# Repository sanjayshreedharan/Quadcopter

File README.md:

# Quadcopter
An Indigenous Low cost Autopilot System for a Quadcopter using Arduino UNO/ FPGA.
 
This project endeavours to design a low cost indigenous auto-pilot system for a quadcopter using the Arduino UNO. This tutorial majorly deals only with the design and deployment of the autopilot system and we assume that you already have the frame, motors, ESC’s and the Lipo Batteries in place. This project also includes the PCB schematic on which our firmware is run.  

# Video

# Deployment Instructions
The frame can either be designed or it can be bought. For speedy development, if you don't have much time in your hands I would suggest to go with buying one. 

We obviously designed our own frame and since frame design and construction as such is a huge task, I would follow up with a tutorial for those of you who wish to design your own frames.

After the frame is ready, the next would be to get the motors, ESC’s, propellers and the power supply in place.The rating of the motors, ESC’s and power supply depends on the size of the frame and the pay-load capacity of the quadcopter. 

For autopilot, a 9DOF IMU (Inertial measurements unit), which consists of an accelerometer, gyroscope and a magnetometer is required. For wireless communication, Bluetooth or RC would do the job. We used the Bluetooth as we would be able to keep a watch on the state of the quadcopter through the serial monitor and also send commands. If flying low-heights and debugging is your requirement, go with bluetooth. For those of you who wish to fly great heights, use a RC module. 

The MPU6050 (6 DOF IMU with accelerometer and gyroscope) and HMC5883L(Magnetometer) was combined to give the quadcopter 9 degrees of freedom. The HC-06 module was used as bluetooth.

A custom Arduino UNO shield was designed for the purpose of a quadcopter. The schematic and the board design is available. So, if you know know how to make a PCB, you can make the shield with the MPU6050, HMC5883L and HC-06 on it and it would fit perfectly on top of the UNO.  

If making PCB is not your piece of cake, I would suggest you to connect the sensors with jumper wires. Make sure the connections, that you have made are reliable, if they are not this might pose a serious problem when the quadcopter is on the go.

After this is done, download the code and fuse it into your Arduino UNO.

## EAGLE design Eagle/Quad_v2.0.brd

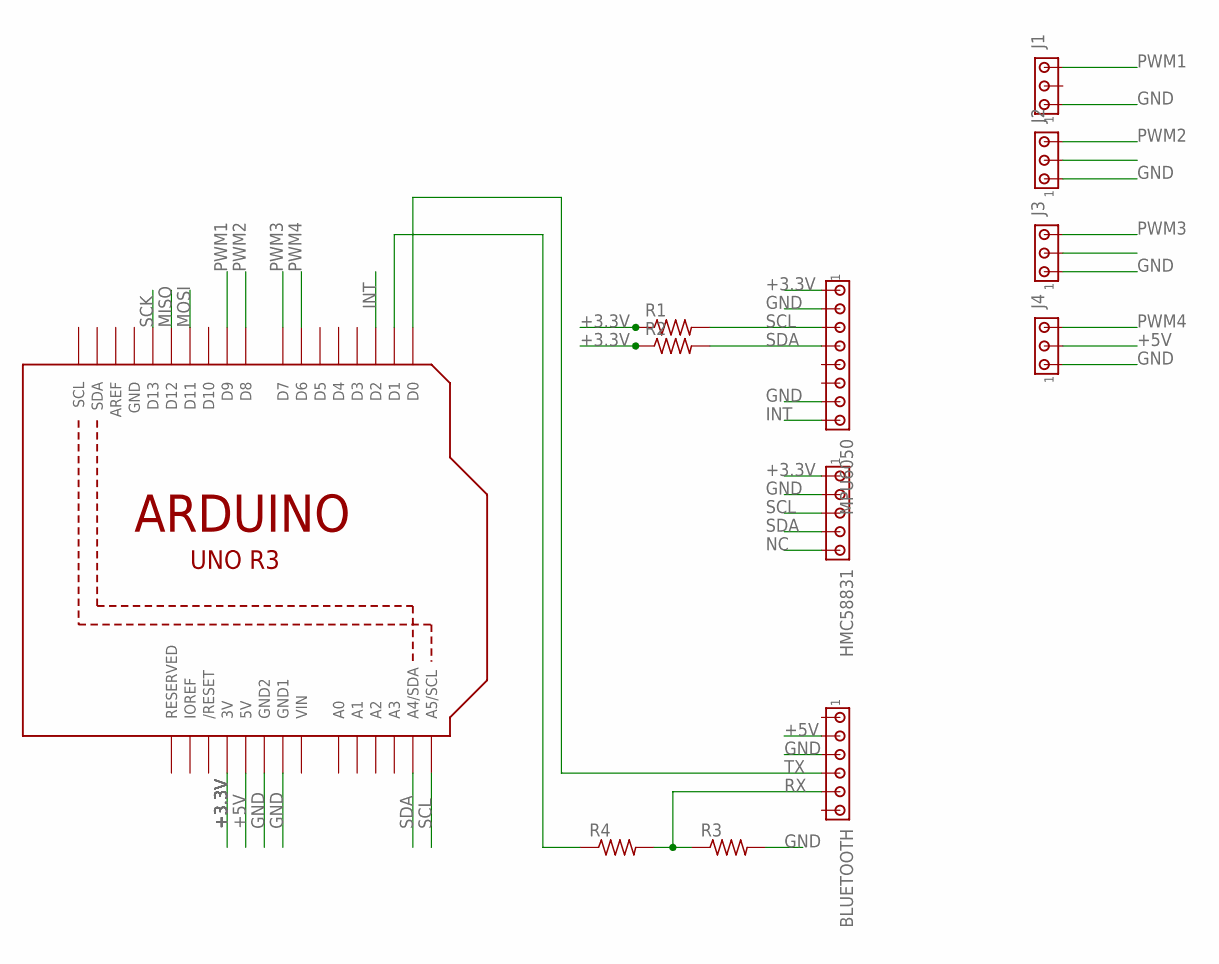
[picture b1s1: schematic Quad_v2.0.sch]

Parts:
BLUETOOTH: MTA06-100; 10X06MTA
HMC58831: MTA05-100; 10X05MTA
J1, J2, J3, J4: MTA03-100; 10X03MTA
MPU6050: MTA08-100; 10X08MTA
R1, R2, R3, R4: R-US_0204/7; 0204/7
U1: ARDUINOR3-DIMENSION; ARDUINOR3

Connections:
+3.3V: HMC58831.1, MPU6050.1, R1.1, R2.1, U1.3V
+5V: BLUETOOTH.5 (2), J4.2, U1.5V
GND: BLUETOOTH.4 (3), HMC58831.2, J1.1, J2.1, J3.1, J4.1, MPU6050.2, MPU6050.7, R3.2, U1.GND, U1.GND1, U1.GND2
INT: MPU6050.8, U1.D2
MISO: U1.D12
MOSI: U1.D11
unnamed: R4.1, U1.D1
NC: HMC58831.5
PWM1: J1.3, U1.D9
PWM2: J2.3, U1.D8
PWM3: J3.3, U1.D7
PWM4: J4.3, U1.D6
RX: BLUETOOTH.2 (5), R3.1, R4.2
SCK: U1.D13
SCL: HMC58831.3, MPU6050.3, R1.2, U1.A5 (A5/SCL)
SDA: HMC58831.4, MPU6050.4, R2.2, U1.A4 (A4/SDA)
TX: BLUETOOTH.3 (4), U1.D0
VIN: U1.VIN

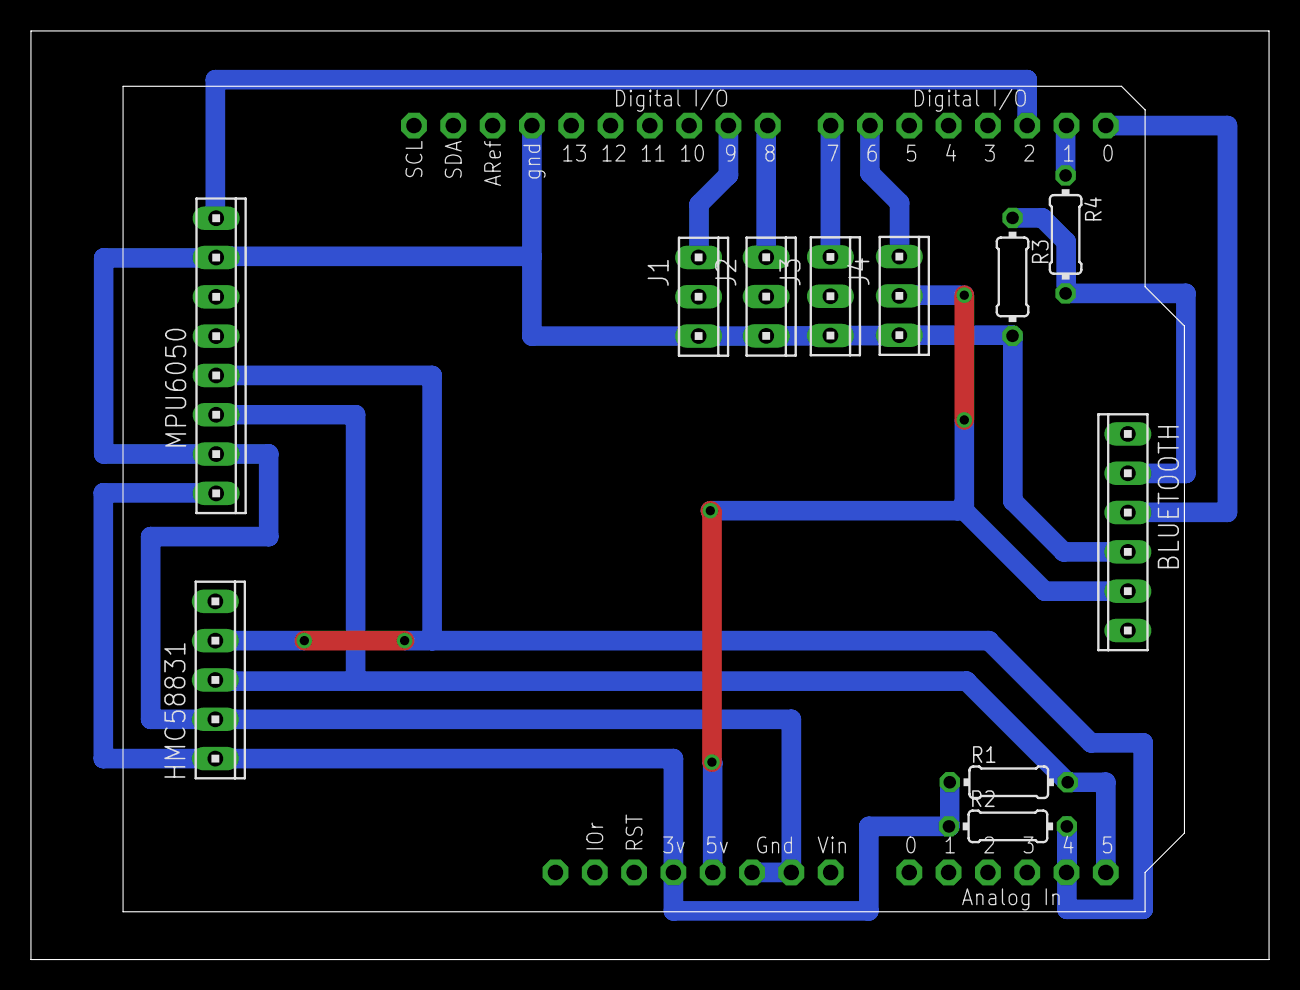
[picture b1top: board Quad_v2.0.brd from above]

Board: 2 copper layers, 80.0 x 60.0 mm, 12 parts (0 on the bottom side), 13 nets.

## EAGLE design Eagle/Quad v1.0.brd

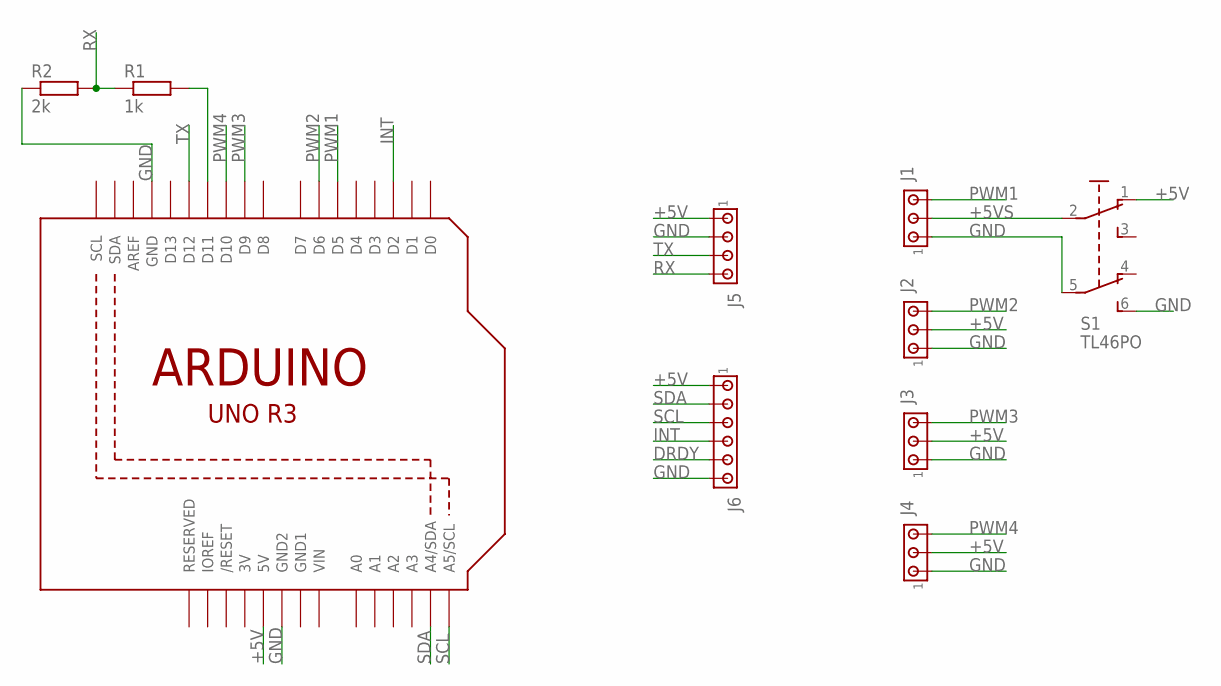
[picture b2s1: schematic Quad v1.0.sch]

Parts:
J1, J2, J3, J4: MTA03-100; 10X03MTA
J5: MTA04-100; 10X04MTA
J6: MTA06-100; 10X06MTA
R1: 1k; 0204/7
R2: 2k; 0204/7
S1: TL46PO; TL4XPO
U1: ARDUINOR3-DIMENSION; ARDUINOR3

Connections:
3V: U1.3V
+5V: J2.2, J3.2, J4.2, J5.1, J6.6 (1), S1.1 (O), U1.5V
+5VS: J1.2, S1.2
DRDY: J6.2 (5)
GND: J1.1, J2.1, J3.1, J4.1, J5.2, J6.1 (6), R2.1, S1.5 (P1), S1.6 (S1), U1.GND, U1.GND2
GND1: U1.GND1
INT: J6.3 (4), U1.D2
unnamed: R1.2, U1.D11
PWM1: J1.3, U1.D5
PWM2: J2.3, U1.D6
PWM3: J3.3, U1.D9
PWM4: J4.3, U1.D10
RX: J5.4, R1.1, R2.2
SCL: J6.4 (3), U1.A5 (A5/SCL)
SDA: J6.5 (2), U1.A4 (A4/SDA)
TX: J5.3, U1.D12
VIN: U1.VIN

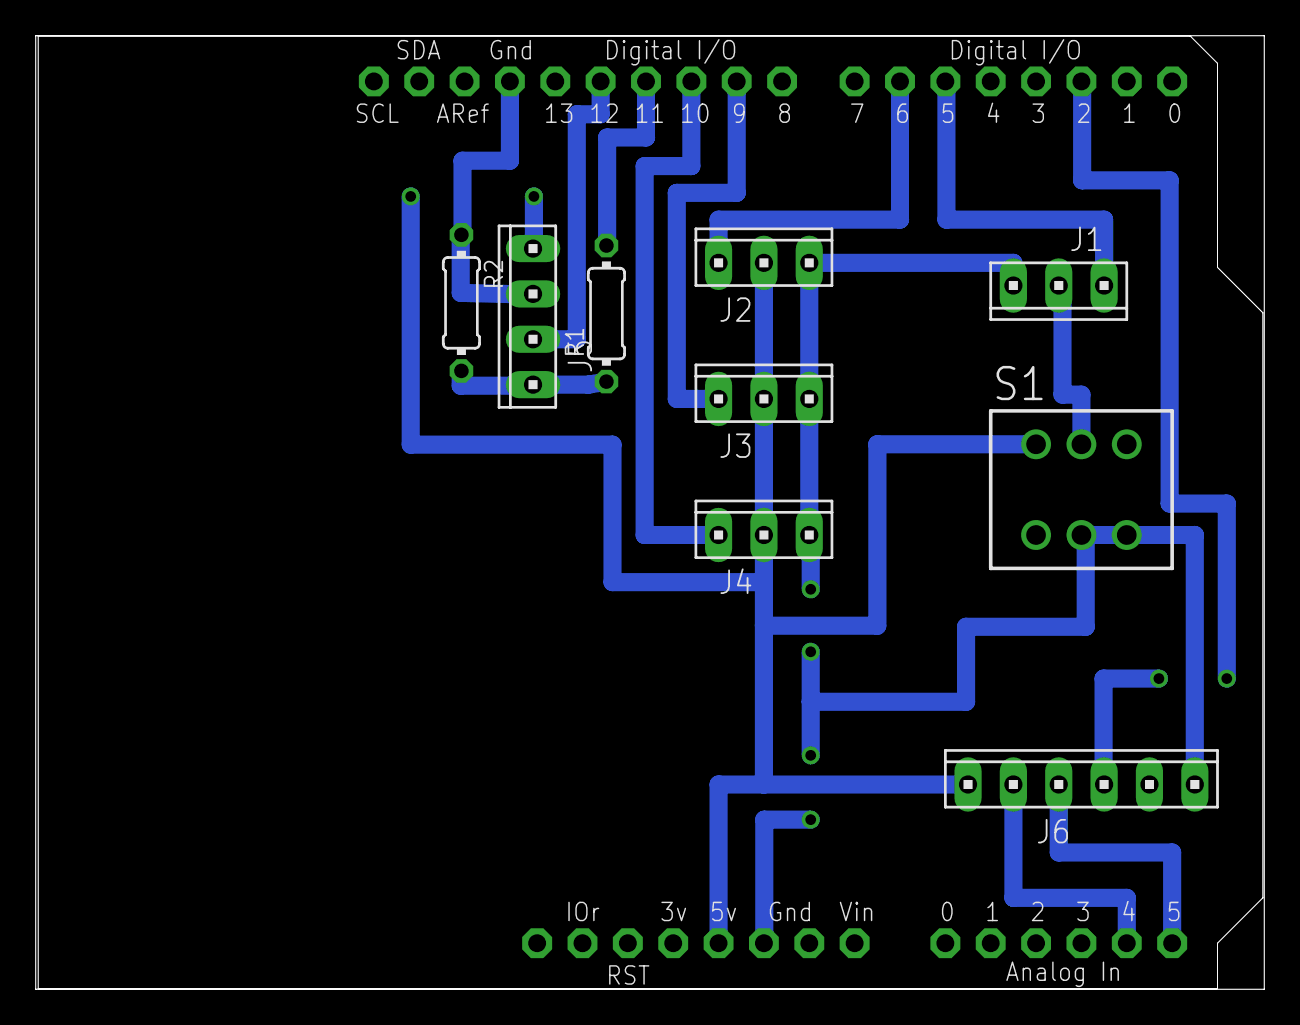
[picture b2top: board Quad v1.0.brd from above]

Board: 2 copper layers, 68.8 x 53.4 mm, 10 parts (0 on the bottom side), 13 nets.

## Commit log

2016-01-31 Create OpenAirTest
2016-11-13 Updated readme with video
2016-11-13 minor changes
2016-12-30 Add v1.0 Eagle CAD PCB files
2016-12-30 Update to v2.0 Eagle CAD PCB Files
